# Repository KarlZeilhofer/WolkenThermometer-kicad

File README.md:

# WolkenThermometer - KiCad-Project

This repository contains the KiCad project of the WolkenThermometer. 
You can find here the bill of materials, the schematic and the board layout. 

Please refer to the project website
http://www.zeilhofer.co.at/wolke

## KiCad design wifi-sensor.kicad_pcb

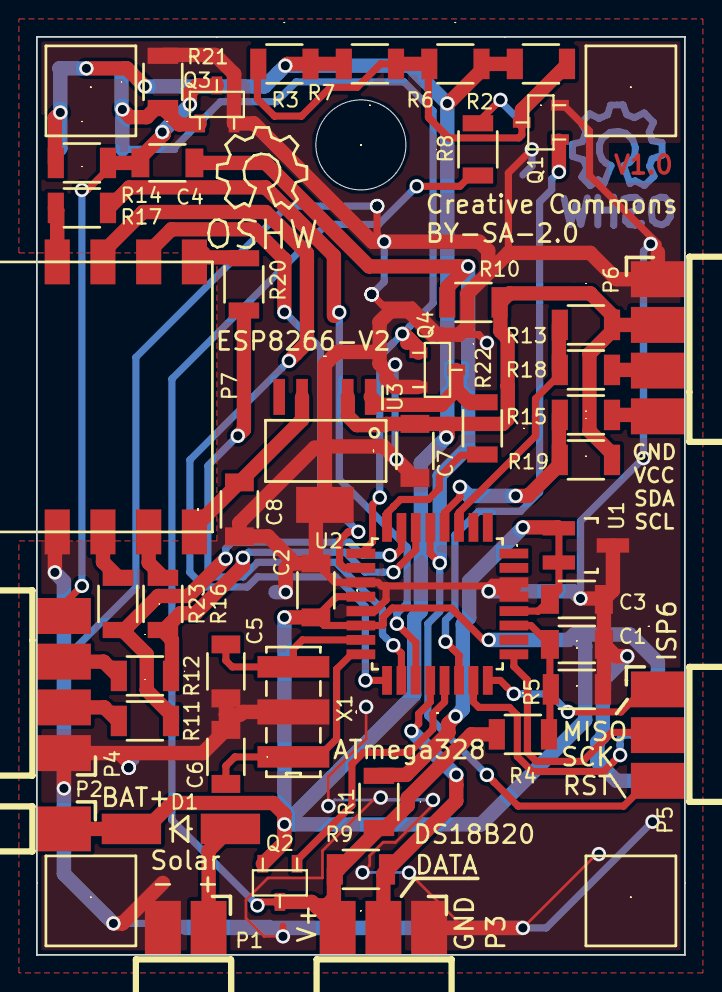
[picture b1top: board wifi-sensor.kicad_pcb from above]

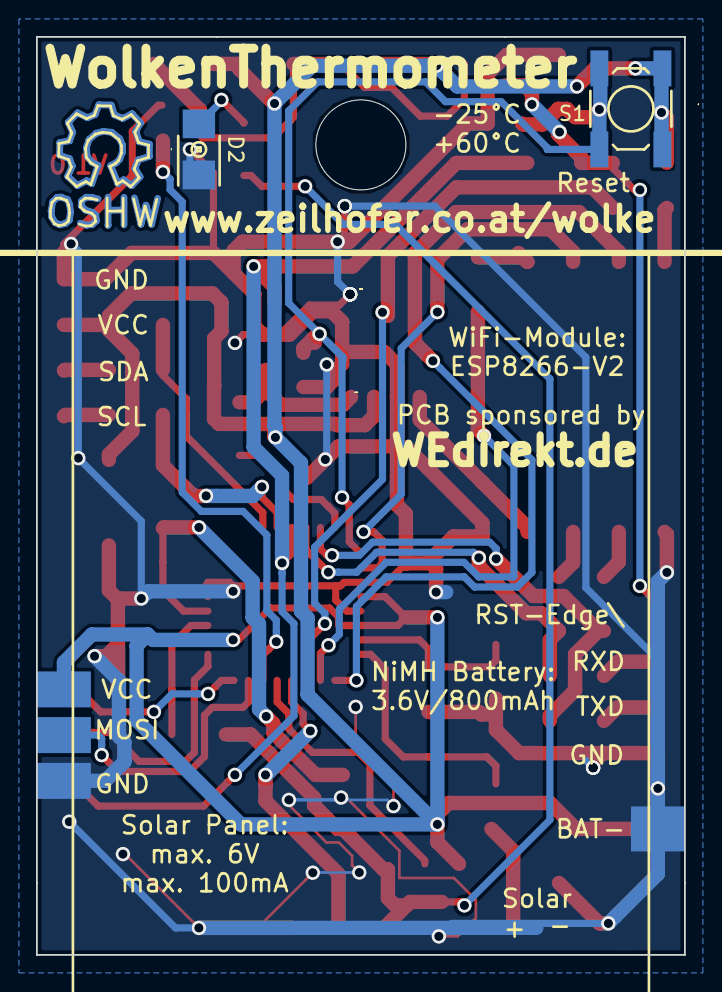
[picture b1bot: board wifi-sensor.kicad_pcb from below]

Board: 2 copper layers, 36.0 x 51.0 mm, 59 parts (6 on the bottom side), 38 nets.

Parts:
BAT1: 3.6V/800mAh/NiMH; Battery-Pack-3xAAA
C1, C3, C4: 100n; C_1206
C2, C7, C8: 10u/10V/X7R; C_1206
C5, C6: DNP; C_1206
D1: LL4148; Diode-MiniMELF_Handsoldering
D2: green; LED-1206
Drill-5mm: VAL**; Drill-5mm
G1: Solar Panel 6V/0.5W; Solar-Panel_60x60mm
P1: SolarPanel; Pinheader_01x02_Edge_SMT
P2: Battery; Pinheader_02x01_Edge_SMT
P3: DS18S20; Pinheader_01x03_Edge_SMT
P4: Arduino-Programming; Pinheader_01x04_Edge_SMT
P5: ISP 6-pin; Pinheader_02x03_Edge_SMT
P6: I2C-Bus; Pinheader_01x04_Edge_SMT
P7: WIFI; ESP8266-V2
Q1, Q3, Q4: BSS123; sot23-gsd
Q2: BSS308; sot23-gsd
R1, R4, R5, R8, R10, R11, R12, R17, R20, R22, R23: 1k; R_1206
R2, R3, R6, R7: 150R; R_1206
R9, R18, R19: 4k7; R_1206
R13, R15: 100R; R_1206
R14, R21: 100k; R_1206
R16: 10k; R_1206
Ref**: Holzfuß; Holzfuss
Ref**#2, Ref**#3, Ref**#4: Holzfuß; Holzfuss
S1: Reset; Switch_SMT_TL3315
Symbol_OSHW-Logo_CopperTop: VAL**; Symbol_OSHW-Logo_CopperTop
Symbol_OSHW-Logo_SilkScreen: VAL**; Symbol_OSHW-Logo_SilkScreen
Symbol_OSHW-Logo_SilkScreen#2: VAL**; Symbol_OSHW-Logo_SilkScreen
U1: LM431SCCM32X; SOT23_Handsoldering
U2: ATMEGA328P-A; TQFP-32_7x7mm_Pitch0.8mm
U3: MCP1825T-3002E_DCCT; SOT-223-5_1.27mm-pitch
X1: RESONATOR 8MHz; Resonator_7.2x3mm

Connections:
/A4: R13.1, R18.2, U2.27
/A5: R15.1, R19.2, U2.28
/A6: C1.1, R4.1, R5.2, U2.19
/Ard.RST\: C4.2, P4.4, Q3.D, R14.1
/CH_PD\: P7.3, R20.2
/D2: R22.1, U2.32
/D3: Q3.G, Q4.G, R21.2, S1.1, U2.1
/D4: P7.6, U2.2
/D5: P7.4, U2.9
/D6: R20.1, U2.10
/D7: R17.1, U2.11
/D8: P3.2, R9.2, U2.12
/D9: Q2.G, U2.13
/D10: Q1.G, U2.14
/D11: P5.4, U2.15
/D12: P5.1, U2.16
/D13: P5.3, U2.17
/RST\: C4.1, P5.5, R10.1, U2.29
/RST\_WiFi: P7.5, R17.2
/RXD: R12.1, R16.1, U2.30
/TXD: R11.1, R23.1, U2.31
/URXD: P7.8, R23.2
/UTXD: P7.1, R16.2
/VCC_WiFi: C8.1, P7.7, U3.4
/XTAL1: C5.1, U2.7, X1.3
/XTAL2: C6.1, U2.8, X1.1
GND: C1.2, C2.2, C3.2, C5.2, C6.2, C7.2, C8.2, D2.K, P1.2, P2.2, P3.1, P4.1, P5.6, P6.1, P7.2, Q1.S, Q3.S, Q4.S, R5.1, R21.1, U1.3, U2.3, U2.5, U2.21, U2.22, U3.3, U3.6, X1.2
unnamed: C3.1, R1.2, U1.1, U1.2, U2.20
unnamed: D1.A, P1.1
unnamed: D2.A, R8.1
unnamed: P3.3, Q2.D, R1.1, R4.2, R8.2, R9.1
unnamed: P4.2, R11.2
unnamed: P4.3, R12.2
unnamed: P6.3, R13.2
unnamed: P6.4, R15.2
unnamed: Q1.D, R2.2, R3.2, R6.2, R7.2
unnamed: Q4.D, R22.2, U3.1
VCC: C2.1, C7.1, D1.K, P2.1, P5.2, P6.2, Q2.S, R2.1, R3.1, R6.1, R7.1, R10.2, R14.2, R18.1, R19.1, S1.2, U2.4, U2.6, U2.18, U3.2

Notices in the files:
wifi-sensor.kicad_pcb:
Creative Commons
BY-SA-2.0
